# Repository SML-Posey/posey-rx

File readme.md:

# Posey Ring Platform

This is a simple IMU hardware platform sized to fit in a ring unit.

It includes:

- nRF52832 ARM microtroller with BLE radio
- CEVA BNO086 9-axis IMU
- Lithium-polymer operation and charging

## Author

[Anthony Wertz](https://me.anthonywertz.com)

## License

Shield: [![CC BY-SA 4.0][cc-by-sa-shield]][cc-by-sa]

This work is licensed under a
[Creative Commons Attribution-ShareAlike 4.0 International License][cc-by-sa].

[![CC BY-SA 4.0][cc-by-sa-image]][cc-by-sa]

[cc-by-sa]: http://creativecommons.org/licenses/by-sa/4.0/
[cc-by-sa-image]: https://licensebuttons.net/l/by-sa/4.0/88x31.png
[cc-by-sa-shield]: https://img.shields.io/badge/License-CC%20BY--SA%204.0-lightgrey.svg

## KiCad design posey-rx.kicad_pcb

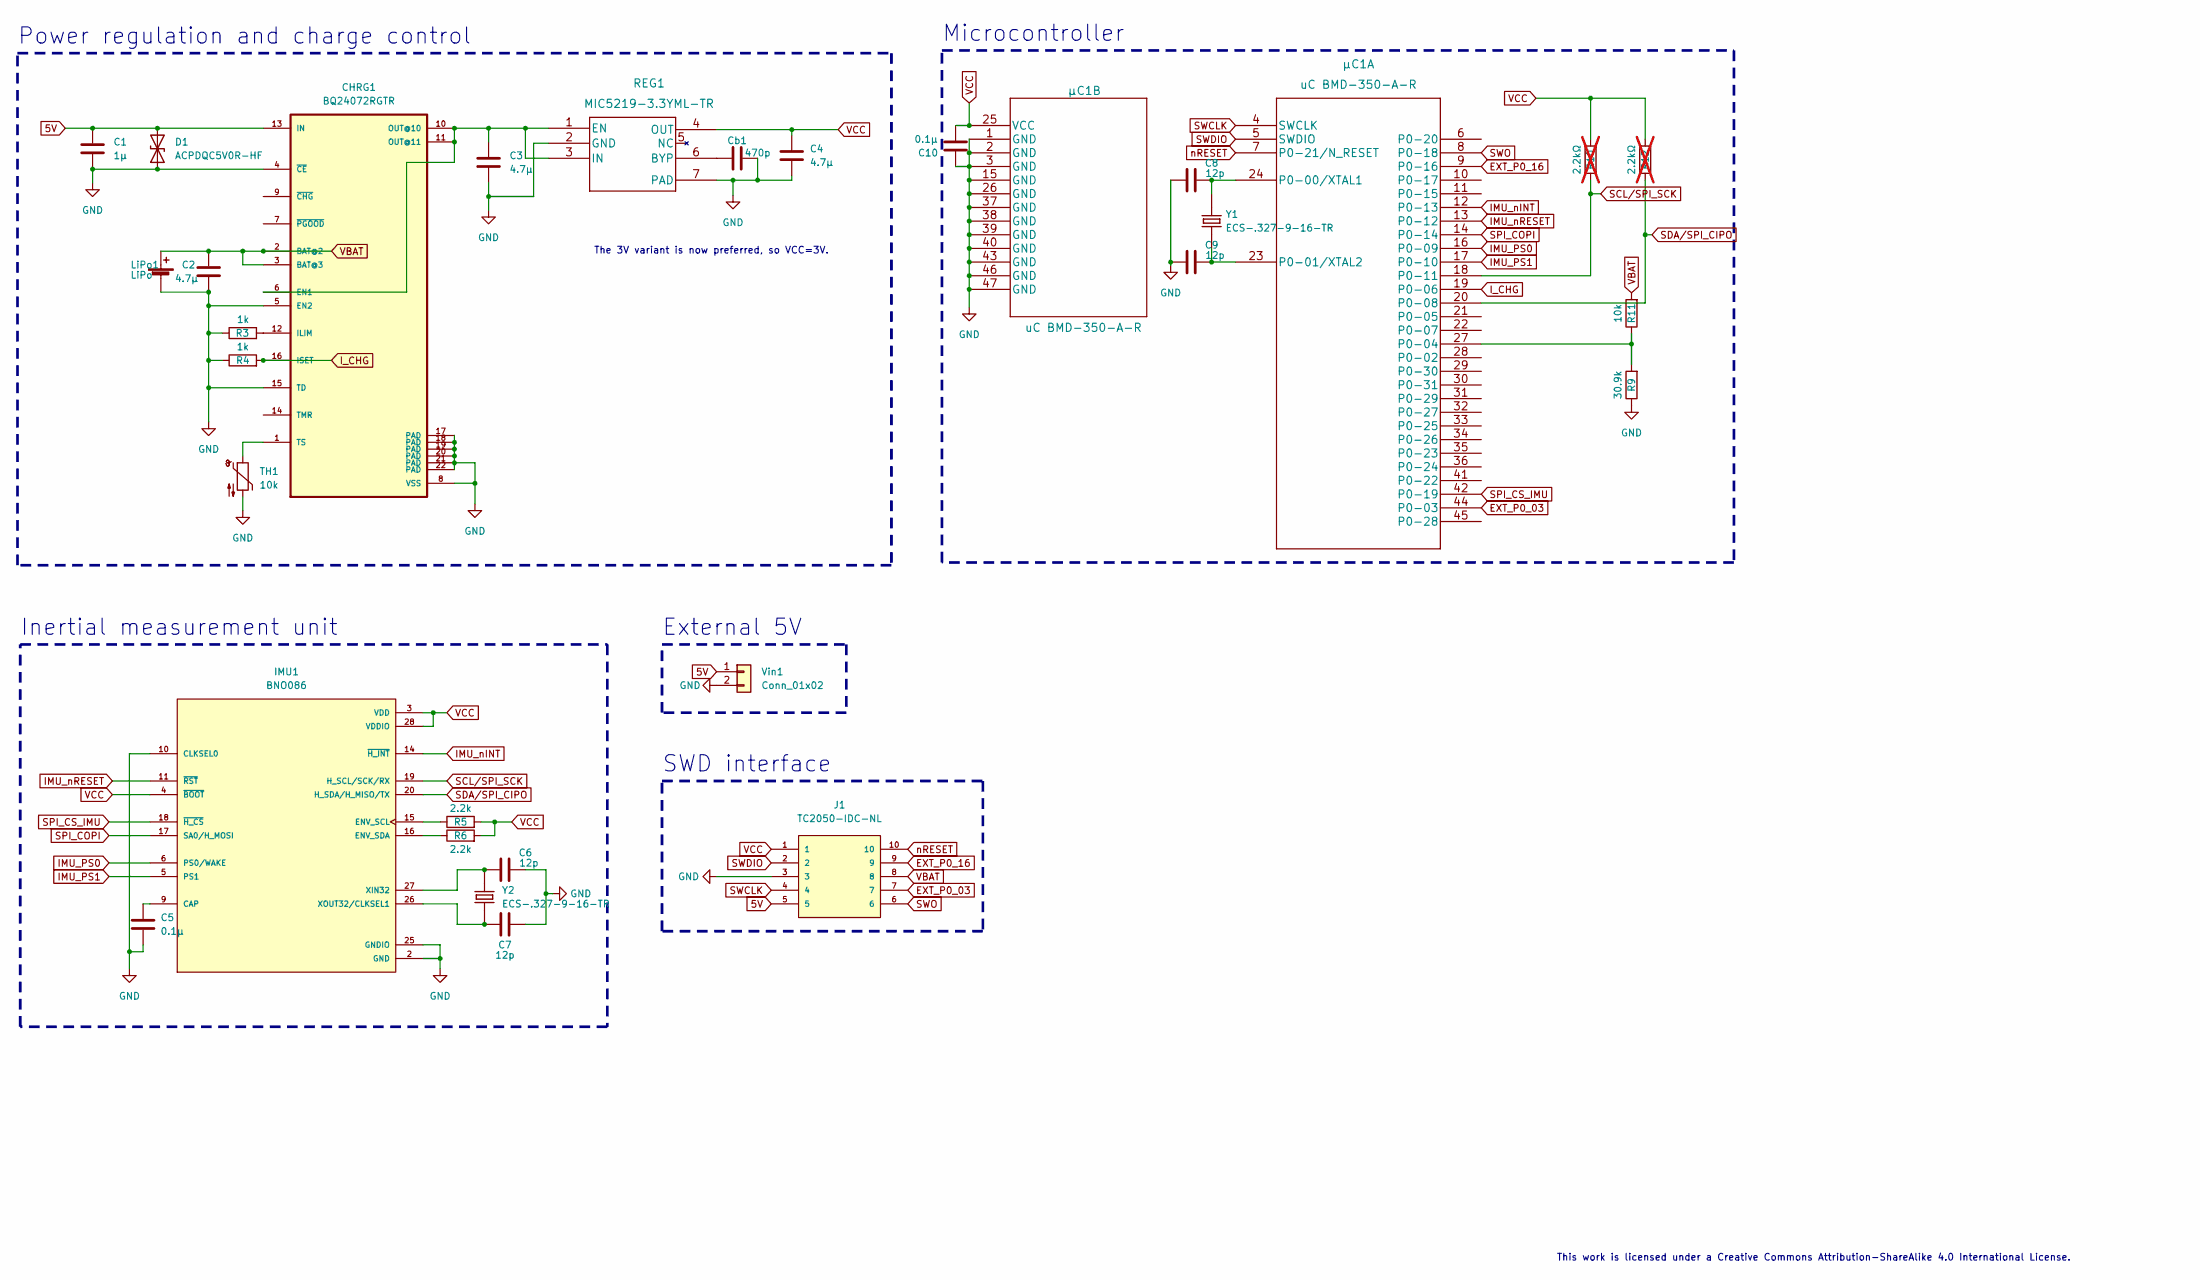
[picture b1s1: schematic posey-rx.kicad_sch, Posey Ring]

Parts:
C1: 1µ; C_0402_1005Metric
C2, C3, C4: 4.7µ; C_0402_1005Metric
C5, C10: 0.1µ; C_0402_1005Metric
C6, C7, C8, C9: 12p; C_0402_1005Metric
CHRG1: BQ24072RGTR; QFN50P300X300X100-17N
Cb1: 470p; C_0402_1005Metric
D1: ACPDQC5V0R-HF; D_0402_1005Metric
IMU1: BNO086; IC_BNO080
J1: TC2050-IDC-NL
LiPo1: LiPo; Split Terminal 2.54
R3, R4: 1k; R_0402_1005Metric
R5, R6: 2.2k; R_0402_1005Metric
R9: 30.9k; R_0402_1005Metric
R10, R12: 2.2kΩ; R_0402_1005Metric; not fitted
R11: 10k; R_0402_1005Metric
REG1: MIC5219-3.3YML-TR
TH1: 10k; R_0402_1005Metric
Vin1: Conn_01x02; Split Terminal 2.54
Y1, Y2: ECS-.327-9-16-TR; XTAL_ECS-.327-9-16-TR
µC1: uC BMD-350-A-R; BMD-350-A-R

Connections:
5V: C1.1, CHRG1.13 (IN), D1.2 (A2), J1.5, Vin1.1
EXT_P0_03: J1.7, µC1.44 (P0-03)
EXT_P0_16: J1.9, µC1.9 (P0-16)
GND: C1.2, C2.1, C3.2, C4.2, C5.2, C6.2, C7.2, C8.1, C9.1, C10.1, CHRG1.4 (~CE), CHRG1.5 (EN2), CHRG1.8 (VSS), CHRG1.15 (TD), CHRG1.17 (PAD), CHRG1.18 (PAD), CHRG1.19 (PAD), CHRG1.20 (PAD), CHRG1.21 (PAD), CHRG1.22 (PAD), Cb1.2, D1.1 (A1), IMU1.2 (GND), IMU1.10 (CLKSEL0), IMU1.25 (GNDIO), J1.3, LiPo1.2 (-), R3.1, R4.1, R9.1, REG1.2 (GND), REG1.7 (PAD), TH1.2, Vin1.2, µC1.1 (GND), µC1.2 (GND), µC1.3 (GND), µC1.15 (GND), µC1.26 (GND), µC1.37 (GND), µC1.38 (GND), µC1.39 (GND), µC1.40 (GND), µC1.43 (GND), µC1.46 (GND), µC1.47 (GND)
IMU_PS0: IMU1.6 (PS0/WAKE), µC1.16 (P0-09)
IMU_PS1: IMU1.5 (PS1), µC1.17 (P0-10)
IMU_nINT: IMU1.14 (~H_INT), µC1.12 (P0-13)
IMU_nRESET: IMU1.11 (~RST), µC1.13 (P0-12)
I_CHG: CHRG1.16 (ISET), R4.2, µC1.19 (P0-06)
unnamed: C3.1, CHRG1.6 (EN1), CHRG1.10 (OUT@10), CHRG1.11 (OUT@11), REG1.1 (EN), REG1.3 (IN)
unnamed: CHRG1.12 (ILIM), R3.2
unnamed: CHRG1.1 (TS), TH1.1
unnamed: C5.1, IMU1.9 (CAP)
unnamed: IMU1.15 (ENV_SCL), R5.1
unnamed: IMU1.16 (ENV_SDA), R6.1
unnamed: C6.1, IMU1.27 (XIN32), Y2.2
unnamed: C7.1, IMU1.26 (XOUT32/CLKSEL1), Y2.1
unnamed: Cb1.1, REG1.6 (BYP)
unnamed: C8.2, Y1.1, µC1.24 (P0-00/XTAL1)
unnamed: C9.2, Y1.2, µC1.23 (P0-01/XTAL2)
unnamed: R9.2, R11.1, µC1.27 (P0-04)
SCL/SPI_SCK: IMU1.19 (H_SCL/SCK/RX), R10.1, µC1.18 (P0-11)
SDA/SPI_CIPO: IMU1.20 (H_SDA/H_MISO/TX), R12.1, µC1.20 (P0-08)
SPI_COPI: IMU1.17 (SA0/H_MOSI), µC1.14 (P0-14)
SPI_CS_IMU: IMU1.18 (~H_CS), µC1.42 (P0-19)
SWCLK: J1.4, µC1.4 (SWCLK)
SWDIO: J1.2, µC1.5 (SWDIO)
SWO: J1.6, µC1.8 (P0-18)
VBAT: C2.2, CHRG1.2 (BAT@2), CHRG1.3 (BAT@3), J1.8, LiPo1.1 (+), R11.2
VCC: C4.1, C10.2, IMU1.3 (VDD), IMU1.4 (~BOOT), IMU1.28 (VDDIO), J1.1, R5.2, R6.2, R10.2, R12.2, REG1.4 (OUT), µC1.25 (VCC)
nRESET: J1.10, µC1.7 (P0-21/N_RESET)

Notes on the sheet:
Power regulation and charge control
Microcontroller
External 5V
The 3V variant is now preferred, so VCC=3V.
Inertial measurement unit
This work is licensed under a Creative Commons Attribution-ShareAlike 4.0 International License.
SWD interface

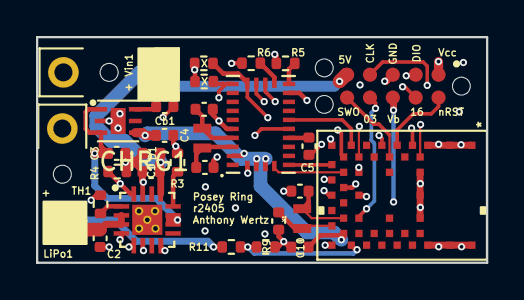
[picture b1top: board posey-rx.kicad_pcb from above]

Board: 6 copper layers, 25.0 x 12.5 mm, 30 parts (0 on the bottom side), 31 nets.

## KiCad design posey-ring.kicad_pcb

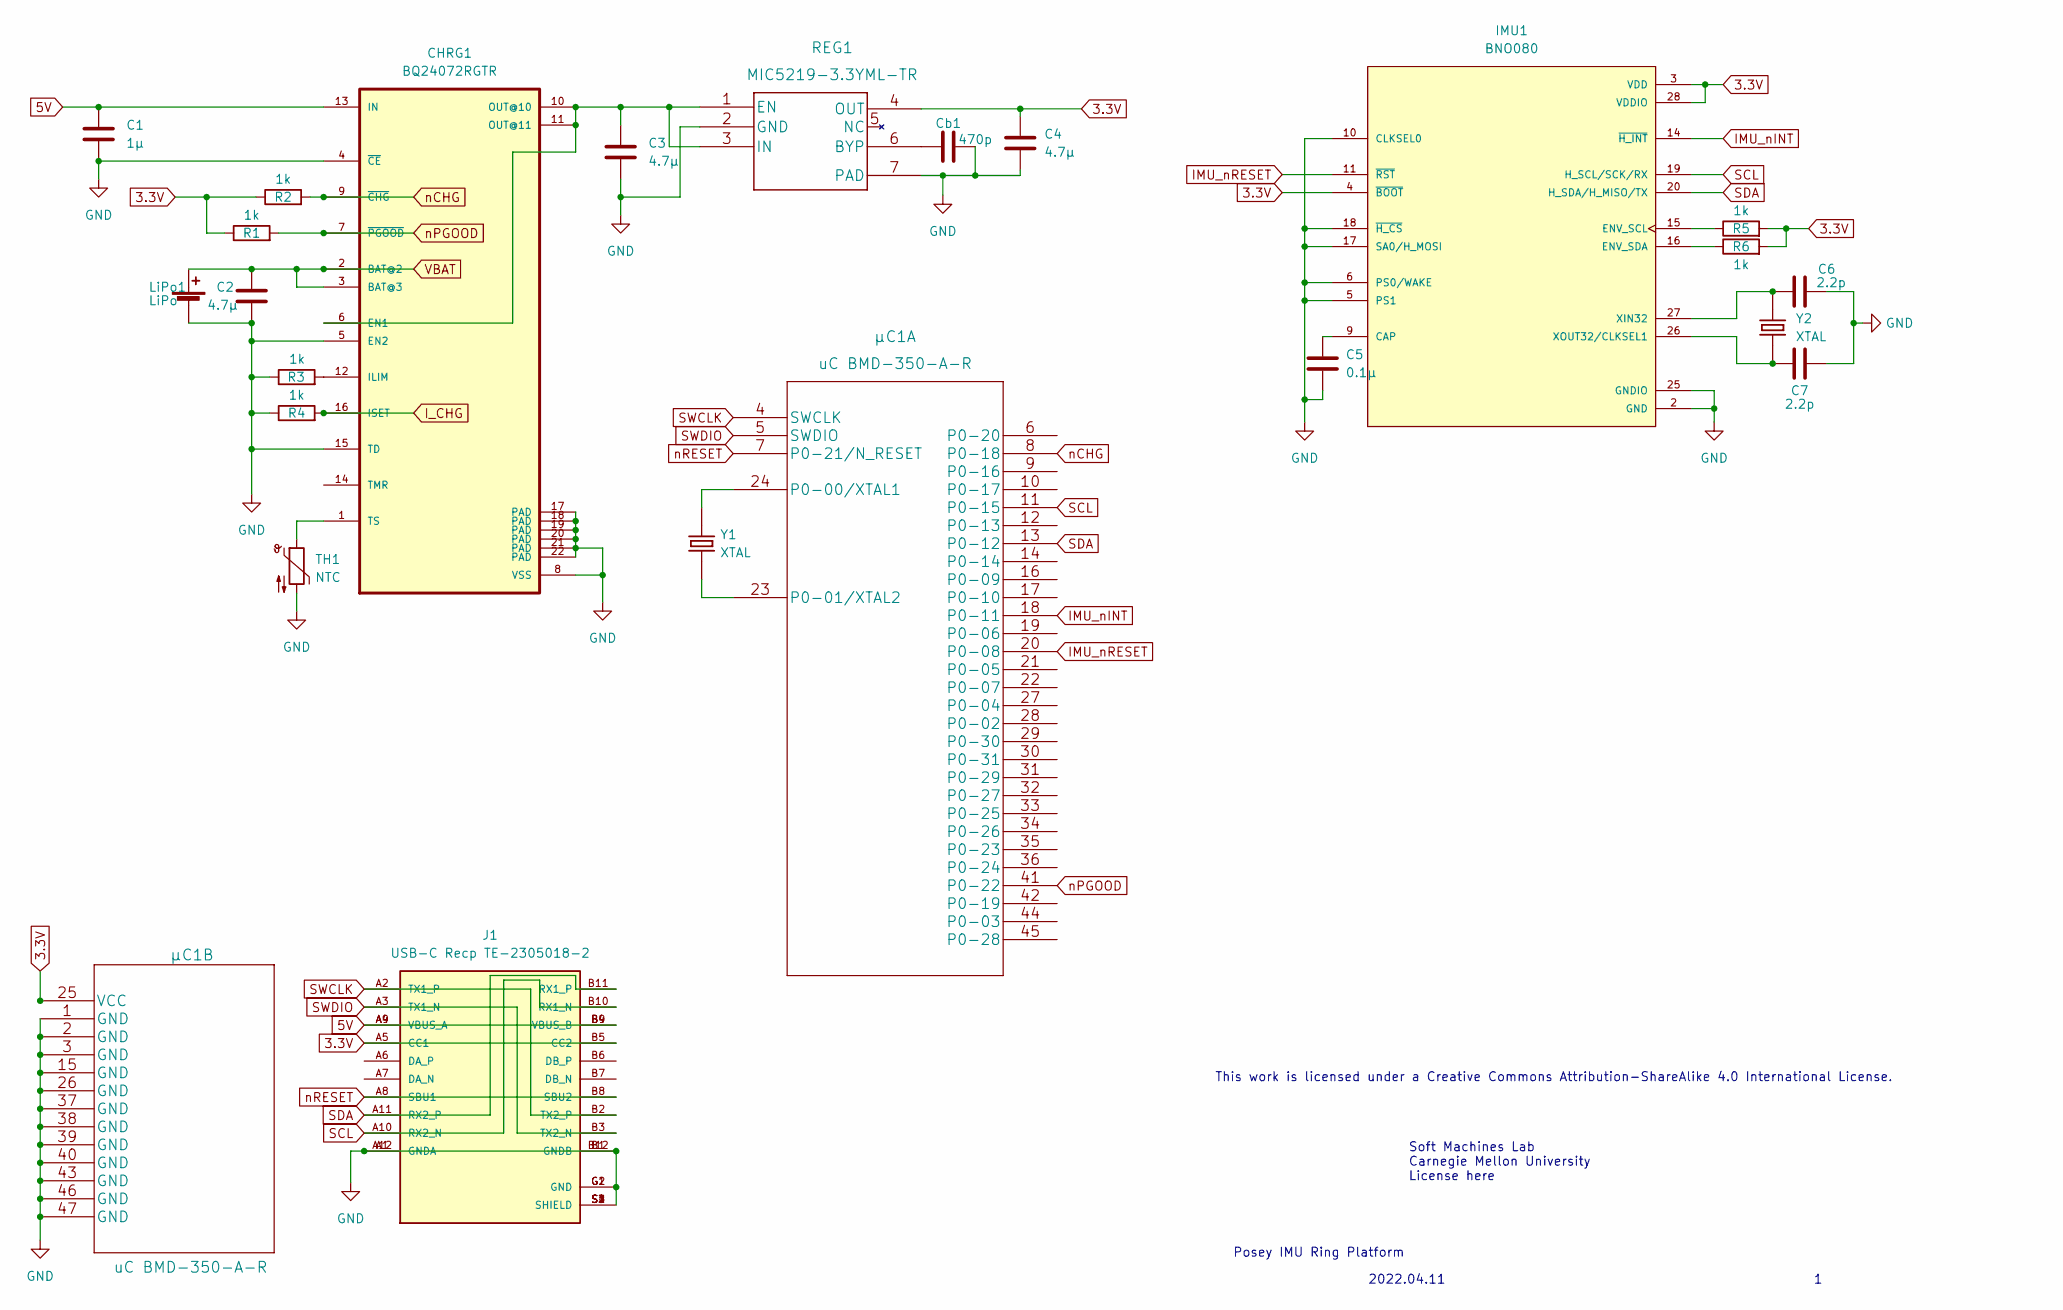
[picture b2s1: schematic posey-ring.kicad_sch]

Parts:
C1: 1µ; C_0402_1005Metric
C2, C3, C4: 4.7µ; C_0402_1005Metric
C5: 0.1µ; C_0402_1005Metric
C6, C7: 2.2p; C_0402_1005Metric
CHRG1: BQ24072RGTR; QFN50P300X300X100-17N-noholes
Cb1: 470p; C_0402_1005Metric
IMU1: BNO080; IC_BNO080
J1: USB-C Recp TE-2305018-2; TE_2305018-2_USBC_Recepticle
LiPo1: LiPo; PinHeader_1x02_P1.00mm_Vertical
R1, R2, R3, R4, R5, R6: 1k; R_0402_1005Metric
REG1: MIC5219-3.3YML-TR
TH1: NTC; R_0402_1005Metric
Y1, Y2: XTAL; XTAL_ECS-.327-9-16-TR
µC1: uC BMD-350-A-R; BMD-350-A-R

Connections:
3.3V: C4.1, IMU1.3 (VDD), IMU1.4 (~BOOT), IMU1.28 (VDDIO), J1.A5 (CC1), J1.B5 (CC2), R1.1, R2.1, R5.2, R6.2, REG1.4 (OUT), µC1.25 (VCC)
5V: C1.1, CHRG1.13 (IN), J1.A4 (VBUS_A), J1.A9 (VBUS_A), J1.B4 (VBUS_B), J1.B9 (VBUS_B)
GND: C1.2, C2.1, C3.2, C4.2, C5.2, C6.2, C7.2, CHRG1.4 (~CE), CHRG1.5 (EN2), CHRG1.8 (VSS), CHRG1.15 (TD), CHRG1.17 (PAD), CHRG1.18 (PAD), CHRG1.19 (PAD), CHRG1.20 (PAD), CHRG1.21 (PAD), CHRG1.22 (PAD), Cb1.2, IMU1.2 (GND), IMU1.5 (PS1), IMU1.6 (PS0/WAKE), IMU1.10 (CLKSEL0), IMU1.17 (SA0/H_MOSI), IMU1.18 (~H_CS), IMU1.25 (GNDIO), J1.A1 (GNDA), J1.A12 (GNDA), J1.B1 (GNDB), J1.B12 (GNDB), J1.G1 (GND), J1.G2 (GND), J1.S1 (SHIELD), J1.S2 (SHIELD), J1.S3 (SHIELD), J1.S4 (SHIELD), LiPo1.2 (-), R3.1, R4.1, REG1.2 (GND), REG1.7 (PAD), TH1.2, µC1.1 (GND), µC1.2 (GND), µC1.3 (GND), µC1.15 (GND), µC1.26 (GND), µC1.37 (GND), µC1.38 (GND), µC1.39 (GND), µC1.40 (GND), µC1.43 (GND), µC1.46 (GND), µC1.47 (GND)
IMU_nINT: IMU1.14 (~H_INT), µC1.18 (P0-11)
IMU_nRESET: IMU1.11 (~RST), µC1.20 (P0-08)
I_CHG: CHRG1.16 (ISET), R4.2
unnamed: C3.1, CHRG1.6 (EN1), CHRG1.10 (OUT@10), CHRG1.11 (OUT@11), REG1.1 (EN), REG1.3 (IN)
unnamed: C5.1, IMU1.9 (CAP)
unnamed: C6.1, IMU1.27 (XIN32), Y2.2
unnamed: C7.1, IMU1.26 (XOUT32/CLKSEL1), Y2.1
unnamed: CHRG1.1 (TS), TH1.1
unnamed: CHRG1.12 (ILIM), R3.2
unnamed: Cb1.1, REG1.6 (BYP)
unnamed: IMU1.15 (ENV_SCL), R5.1
unnamed: IMU1.16 (ENV_SDA), R6.1
unnamed: Y1.1, µC1.24 (P0-00/XTAL1)
unnamed: Y1.2, µC1.23 (P0-01/XTAL2)
SCL: IMU1.19 (H_SCL/SCK/RX), J1.A10 (RX2_N), J1.B10 (RX1_N), µC1.11 (P0-15)
SDA: IMU1.20 (H_SDA/H_MISO/TX), J1.A11 (RX2_P), J1.B11 (RX1_P), µC1.13 (P0-12)
SWCLK: J1.A2 (TX1_P), J1.B2 (TX2_P), µC1.4 (SWCLK)
SWDIO: J1.A3 (TX1_N), J1.B3 (TX2_N), µC1.5 (SWDIO)
VBAT: C2.2, CHRG1.2 (BAT@2), CHRG1.3 (BAT@3), LiPo1.1 (+)
nCHG: CHRG1.9 (~CHG), R2.2, µC1.8 (P0-18)
nPGOOD: CHRG1.7 (~PGOOD), R1.2, µC1.41 (P0-22)
nRESET: J1.A8 (SBU1), J1.B8 (SBU2), µC1.7 (P0-21/N_RESET)

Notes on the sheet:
Soft Machines Lab Carnegie Mellon University License here
2022.04.11
Posey IMU Ring Platform
This work is licensed under a Creative Commons Attribution-ShareAlike 4.0 International License.

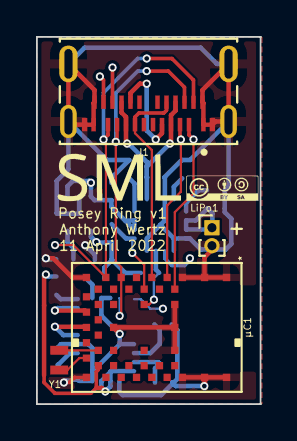
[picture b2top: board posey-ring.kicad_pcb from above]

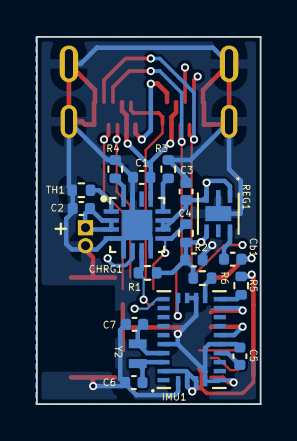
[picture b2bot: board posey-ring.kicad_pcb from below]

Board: 4 copper layers, 12.4 x 20.4 mm, 23 parts (19 on the bottom side), 25 nets.

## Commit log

2022-04-11 Initial
2022-04-24 Updated license and step.
2022-12-05 Updated to r2
2023-10-25 r2310
2024-07-01 Updated readme, license, and version.
2024-07-01 Added license.
2024-07-01 Updated readme.
